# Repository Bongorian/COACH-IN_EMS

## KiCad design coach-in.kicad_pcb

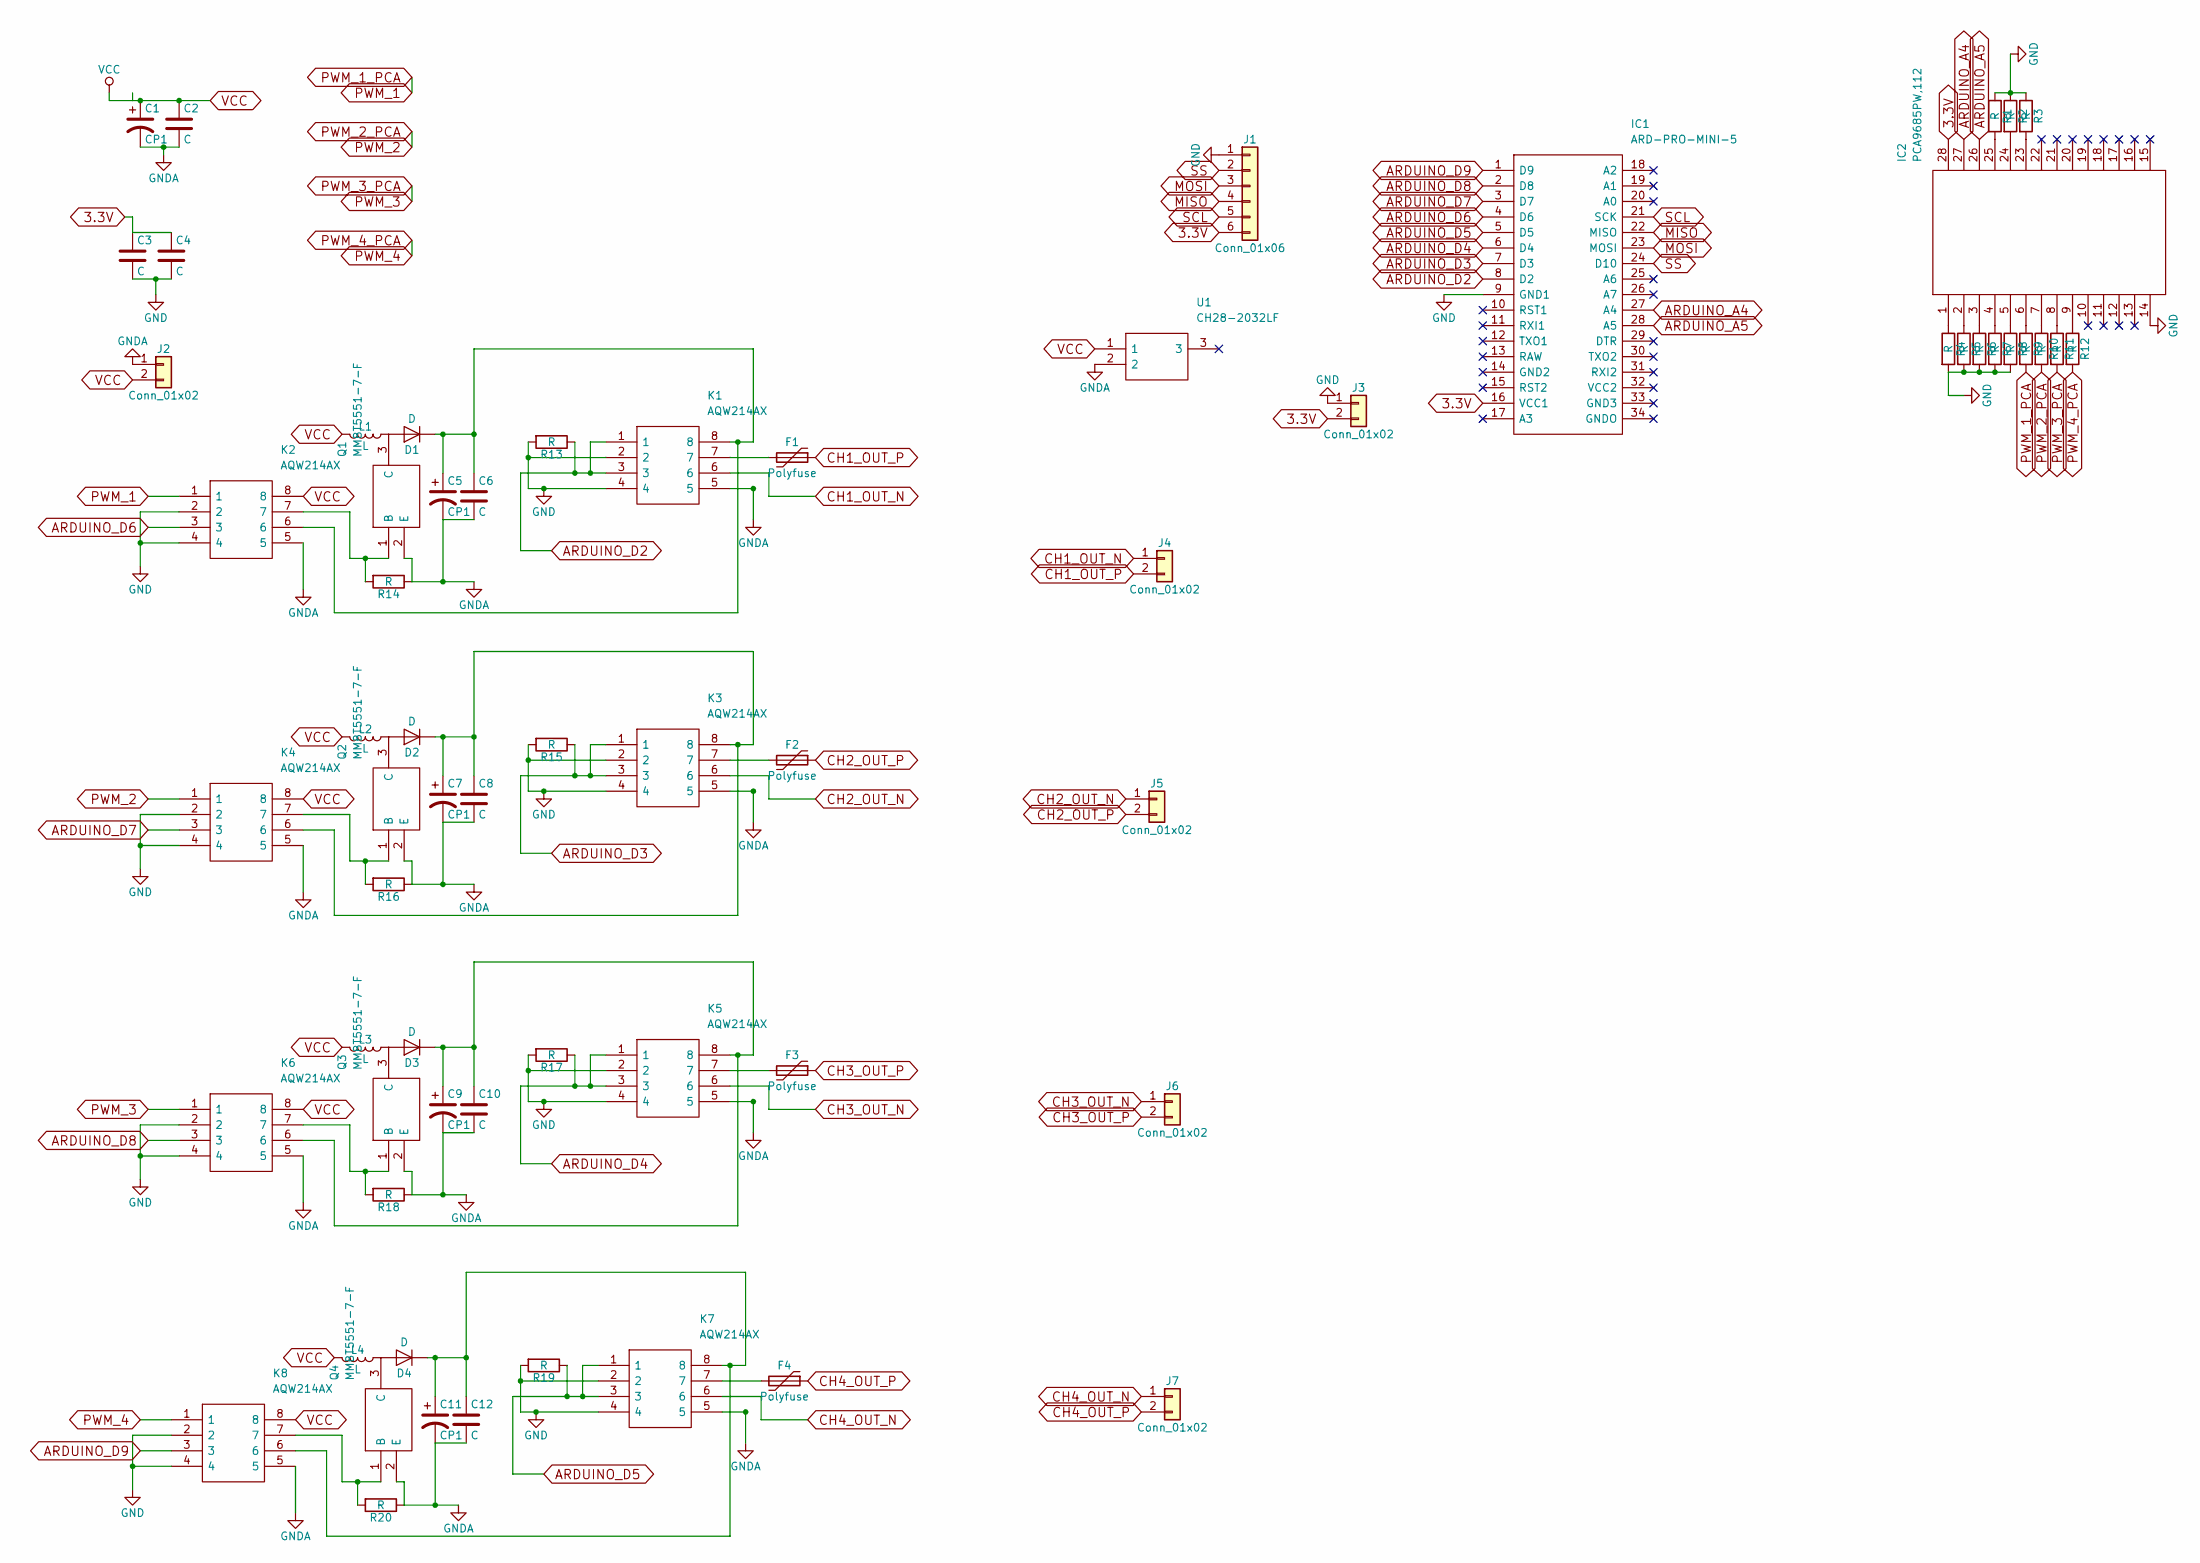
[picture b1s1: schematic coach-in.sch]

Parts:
C1, C5, C7, C9, C11: CP1; CP_Elec_5x5.3
C2, C3, C4, C6, C10, C12: C; C_0603_HandSoldering
C8: C; C_0603
D1, D2, D3, D4: D; D_SOD-123
F1, F2, F3, F4: Polyfuse; R_Axial_DIN0411_L9.9mm_D3.6mm_P5.08mm_Vertical
IC1: ARD-PRO-MINI-5; ARDPROMINI5; Manufacturer_Part_Number ARD-PRO-MINI-5
IC2: PCA9685PW,112; SOP65P640X110-28N; Manufacturer_Part_Number PCA9685PW,112
J1: Conn_01x06; Pin_Header_Straight_1x06_Pitch2.54mm
J2, J3: Conn_01x02; Pin_Header_Straight_1x02_Pitch2.54mm
J4, J5, J6, J7: Conn_01x02; JST_PH_B2B-PH-K_02x2.00mm_Straight
K1, K2, K3, K4, K5, K6, K7, K8: AQW214AX; SOP254P962X390-8N; Manufacturer_Part_Number AQW214AX
L1, L2, L3, L4: L; L_Axial_L7.0mm_D3.3mm_P10.16mm_Horizontal_Fastron_MICC
Q1, Q2, Q3, Q4: MMBT5551-7-F; SOT96P240X110-3N; Manufacturer_Part_Number MMBT5551-7-F
R1, R2, R3, R4, R5, R6, R7, R8, R9, R10, R11, R12, R13, R14, R15, R16, R17, R18, R19, R20: R; R_0603_HandSoldering
U1: CH28-2032LF; CH282032LF; Manufacturer_Part_Number CH28-2032LF

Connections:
3.3V: C3.1, C4.1, IC1.16 (VCC1), IC2.28, J1.6, J3.2; also elsewhere on the board
ARDUINO_A4: IC1.27 (A4), IC2.27; also elsewhere on the board
ARDUINO_A5: IC1.28 (A5), IC2.26; also elsewhere on the board
ARDUINO_D2: IC1.8 (D2), K1.1, K1.3, R13.1; also elsewhere on the board
ARDUINO_D3: IC1.7 (D3), K3.1, K3.3, R15.1; also elsewhere on the board
ARDUINO_D4: IC1.6 (D4), K5.1, K5.3, R17.1; also elsewhere on the board
ARDUINO_D5: IC1.5 (D5), K7.1, K7.3, R19.1; also elsewhere on the board
ARDUINO_D6: IC1.4 (D6), K2.3; also elsewhere on the board
ARDUINO_D7: IC1.3 (D7), K4.3; also elsewhere on the board
ARDUINO_D8: IC1.2 (D8), K6.3; also elsewhere on the board
ARDUINO_D9: IC1.1 (D9), K8.3; also elsewhere on the board
CH1_OUT_N: J4.1, K1.6
CH1_OUT_P: F1.1, J4.2
CH2_OUT_N: J5.1, K3.6
CH2_OUT_P: F2.1, J5.2
CH3_OUT_N: J6.1, K5.6
CH3_OUT_P: F3.1, J6.2
CH4_OUT_N: J7.1, K7.6
CH4_OUT_P: F4.1, J7.2
GND: C3.2, C4.2, IC1.9 (GND1), IC2.14, J1.1, J3.1, K1.2, K1.4, K2.2, K2.4, K3.2, K3.4, K4.2, K4.4, K5.2, K5.4, K6.2, K6.4, K7.2, K7.4, K8.2, K8.4, R1.1, R2.1, R3.1, R4.2, R5.2, R6.2, R7.2, R8.2, R13.2, R15.2, R17.2, R19.2; also elsewhere on the board
GNDA: C1.2, C2.2, C5.2, C6.2, C7.2, C8.2, C9.2, C10.2, C11.2, C12.2, J2.1, K1.5, K2.5, K3.5, K4.5, K5.5, K6.5, K7.5, K8.5, Q1.2 (E), Q2.2 (E), Q3.2 (E), Q4.2 (E), R14.1, R16.1, R18.1, R20.1, U1.2; also elsewhere on the board
unnamed: C5.1, C6.1, D1.1 (K), K1.8, K2.6
unnamed: C7.1, C8.1, D2.1 (K), K3.8, K4.6
unnamed: C9.1, C10.1, D3.1 (K), K5.8, K6.6
unnamed: C11.1, C12.1, D4.1 (K), K7.8, K8.6
unnamed: D1.2 (A), L1.1, Q1.3 (C)
unnamed: D2.2 (A), L2.1, Q2.3 (C)
unnamed: D3.2 (A), L3.1, Q3.3 (C)
unnamed: D4.2 (A), L4.1, Q4.3 (C)
unnamed: F1.2, K1.7
unnamed: F2.2, K3.7
unnamed: F3.2, K5.7
unnamed: F4.2, K7.7
unnamed: IC1.21 (SCK), J1.5
unnamed: IC1.22 (MISO), J1.4
unnamed: IC1.23 (MOSI), J1.3
unnamed: IC1.24 (D10), J1.2
unnamed: IC2.1, R4.1
unnamed: IC2.2, R5.1
unnamed: IC2.3, R6.1
unnamed: IC2.4, R7.1
unnamed: IC2.5, R8.1
unnamed: IC2.6, R9.1
unnamed: IC2.7, R10.1
unnamed: IC2.8, R11.1
unnamed: IC2.9, R12.1
unnamed: IC2.23, R3.2
unnamed: IC2.24, R2.2
unnamed: IC2.25, R1.2
unnamed: K2.7, Q1.1 (B), R14.2
unnamed: K4.7, Q2.1 (B), R16.2
unnamed: K6.7, Q3.1 (B), R18.2
unnamed: K8.7, Q4.1 (B), R20.2
PWM_1: K2.1, R9.2
PWM_2: K4.1, R10.2
PWM_3: K6.1, R11.2
PWM_4: K8.1, R12.2
VCC: C1.1, C2.1, J2.2, K2.8, K4.8, K6.8, K8.8, L1.2, L2.2, L3.2, L4.2, U1.1; also elsewhere on the board

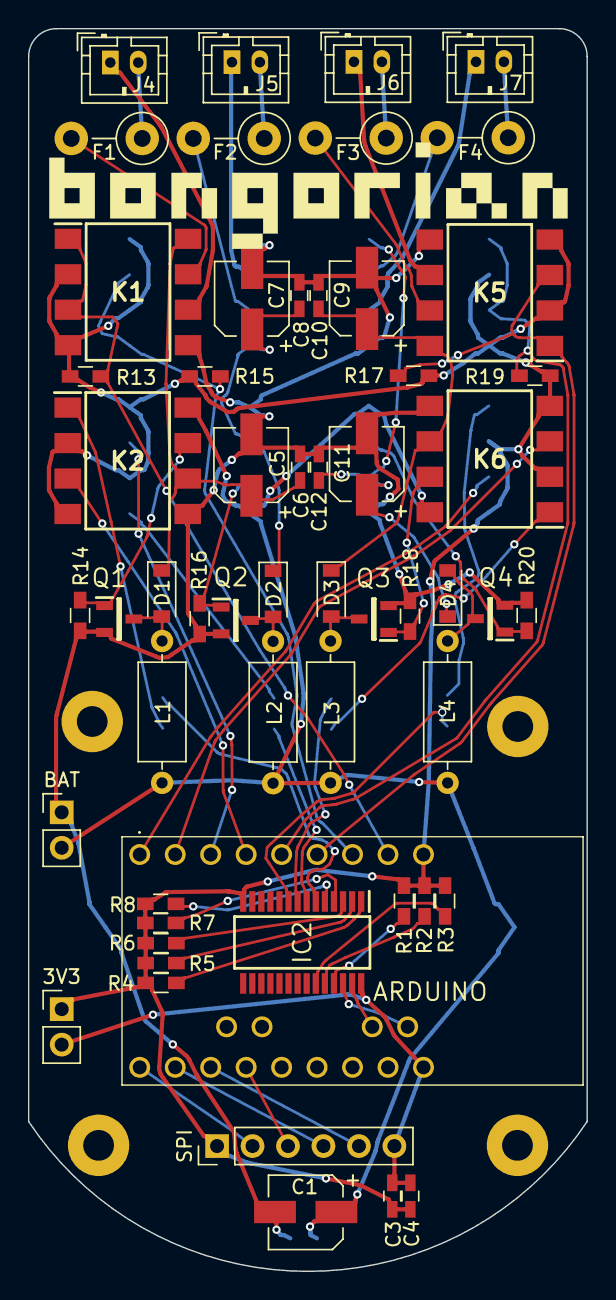
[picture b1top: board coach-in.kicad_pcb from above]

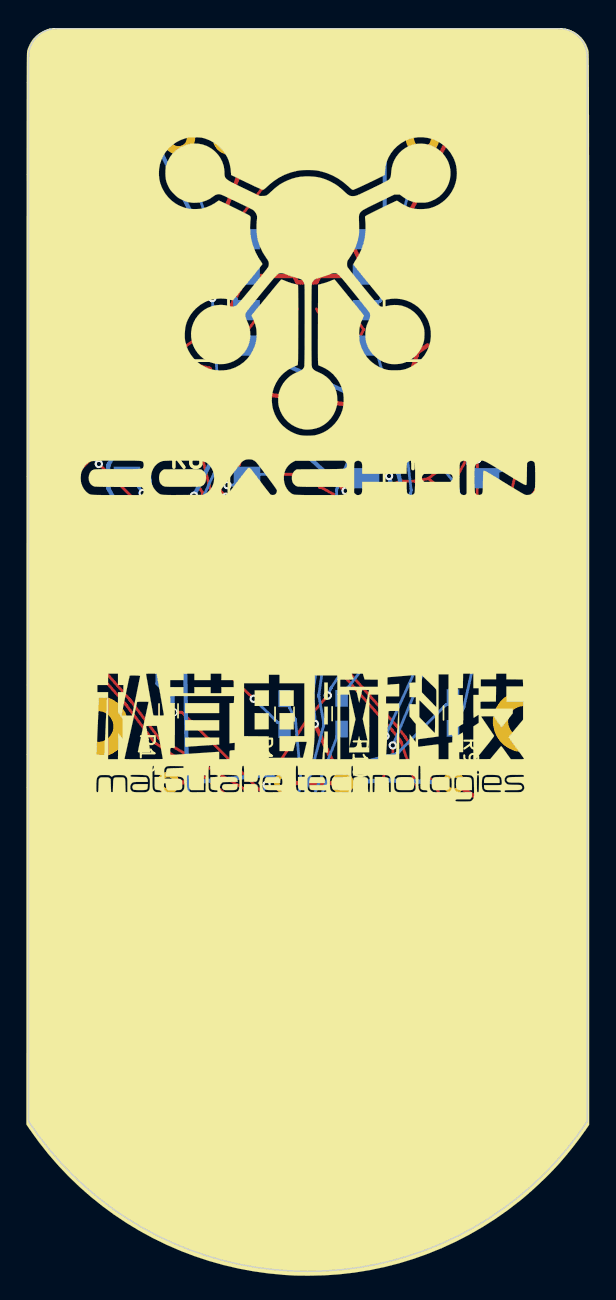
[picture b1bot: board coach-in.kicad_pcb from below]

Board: 2 copper layers, 40.0 x 89.0 mm, 71 parts (11 on the bottom side), 58 nets.

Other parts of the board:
3V3: Conn_01x02; Pin_Header_Straight_1x02_Pitch2.54mm
ARDUINO: ARD-PRO-MINI-5; ARDPROMINI5
BAT: Conn_01x02; Pin_Header_Straight_1x02_Pitch2.54mm
CR2032: CH28-2032LF; CH282032LF
J8, J9, J10, J11: Conn_01x01; MountingHole_2.2mm_M2_Pad
SPI: Conn_01x06; Pin_Header_Straight_1x06_Pitch2.54mm
coachin: LOGO; coachin222

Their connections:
3.3V: 3V3.2, ARDUINO.16, SPI.6; also elsewhere on the board
ARDUINO_A4: ARDUINO.27; also elsewhere on the board
ARDUINO_A5: ARDUINO.28; also elsewhere on the board
ARDUINO_D2: ARDUINO.8; also elsewhere on the board
ARDUINO_D3: ARDUINO.7; also elsewhere on the board
ARDUINO_D4: ARDUINO.6; also elsewhere on the board
ARDUINO_D5: ARDUINO.5; also elsewhere on the board
ARDUINO_D6: ARDUINO.4; also elsewhere on the board
ARDUINO_D7: ARDUINO.3; also elsewhere on the board
ARDUINO_D8: ARDUINO.2; also elsewhere on the board
ARDUINO_D9: ARDUINO.1; also elsewhere on the board
GND: 3V3.1, ARDUINO.9, SPI.1; also elsewhere on the board
GNDA: BAT.1, CR2032.2; also elsewhere on the board
MISO: ARDUINO.22, SPI.5
MOSI: ARDUINO.23, SPI.4
SCL: ARDUINO.21, SPI.3
SS: ARDUINO.24, SPI.2
VCC: BAT.2, CR2032.1; also elsewhere on the board
